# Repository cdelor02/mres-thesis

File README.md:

Thesis for Masters in Research in [Medical Robotics and Image Guided Intervention](https://www.imperial.ac.uk/study/pg/medicine/medical-robotics/) at [Imperial College London](https://www.imperial.ac.uk), 2020-2021.

- Remember to run the setup for EIDORS in MATLAB if it isn't already on the path

Packages and modules used:
- [EIDORS](http://eidors3d.sourceforge.net)
- [gmsh](https://gmsh.info)
- [mesh2matlab](https://github.com/Jimbles/meshio2matlab)
- [OpenCV](https://opencv.org)
- [NumPy](https://numpy.org)
- [Scikit-learn](https://scikit-learn.org/stable/)
- [Tensorflow](https://www.tensorflow.org)
- [Keras](https://keras.io)
- [ffmpeg](https://www.ffmpeg.org)

Resources:
- [Soft robotics toolkit](https://softroboticstoolkit.com/home)

Software used:
- [ParaView](https://www.paraview.org)
- [SolidWorks](https://www.solidworks.com)
- [AutoCAD Inventor (v2021)](https://www.autodesk.co.uk/products/inventor/overview)
- [MATLAB](https://www.mathworks.com/products/matlab.html)
- [LabVIEW](https://www.ni.com/en-gb/shop/labview.html)
- [Arduino](https://www.arduino.cc)

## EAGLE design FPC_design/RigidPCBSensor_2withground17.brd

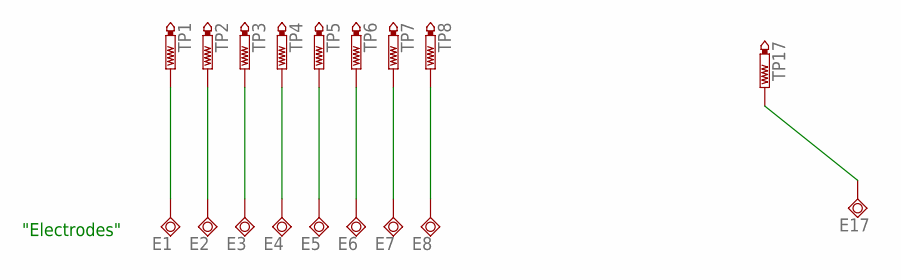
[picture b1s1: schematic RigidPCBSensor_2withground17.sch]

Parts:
E1, E2, E3, E4, E5, E6, E7, E8, E17: TPSQTP15R; TP15R
TP1, TP2, TP3, TP4, TP5, TP6, TP7, TP8, TP17: PTR1; TP10SQLONG

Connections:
unnamed: E1.TP, TP1.TP
unnamed: E2.TP, TP2.TP
unnamed: E3.TP, TP3.TP
unnamed: E4.TP, TP4.TP
unnamed: E5.TP, TP5.TP
unnamed: E6.TP, TP6.TP
unnamed: E7.TP, TP7.TP
unnamed: E8.TP, TP8.TP
unnamed: E17.TP, TP17.TP

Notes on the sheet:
"Electrodes"

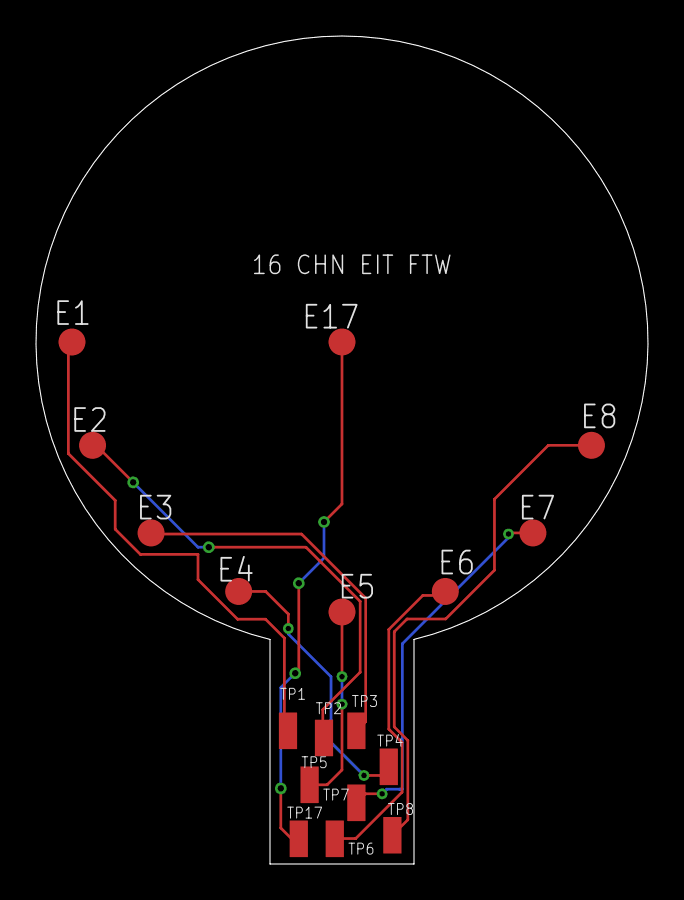
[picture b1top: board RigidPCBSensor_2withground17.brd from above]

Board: 2 copper layers, 34.0 x 46.0 mm, 18 parts (0 on the bottom side), 9 nets.

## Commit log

2021-03-11 start dedicated thesis repo
2021-03-11 simulation work
2021-03-12 sim work
2021-03-16 made hollow version
2021-03-18 work
2021-03-19 Fixed electrode assignment and FWD model check errors in bent finger example
2021-03-20 two bend finger model
2021-03-21 make weekly update presentation
2021-03-23 sim images for slides
2021-03-25 made simple pneunet mesh
2021-03-26 organize and make bent pneunet actuator sim
2021-03-29 second bend pneunet EIDORS model
2021-03-31 weekly meeting
2021-04-06 inflated chambers EIDORS model
2021-04-14 meeting on 14/04/21
2021-04-19 actuator videos
2021-04-21 single chamber EIDORS work
2021-04-22 single chamber stl
2021-04-26 some labview data
2021-04-26 plot labview data
2021-04-27 inflatetest
2021-04-27 labview data
2021-05-05 actuator tube eit data
2021-05-05 general update after weekly meeting
2021-05-10 actuator EIT data
2021-05-17 eit chamber test data
2021-05-25 actuator test eit data
2021-05-28 SDM finger development
2021-06-03 sdm actuator eit test
2021-06-03 fixed sdm actuator eit data
2021-06-03 sdm actuator eit data better
2021-06-07 plots timing test
2021-06-07 parsed/trimmed down actuator data
2021-06-12 poster work
2021-06-23 actuator stepper control
2021-06-29 preliminary full stepper tests
2021-07-01 duetimer test
2021-07-01 more testing
2021-07-06 OpenCV red shape tracking work
2021-07-09 wire impedance measurements with DAQ
2021-07-15 CV progress
2021-07-23 finish cv and neaten up
2021-08-04 create and fill requirements.txt for software
2021-08-04 some eit sync data
2021-08-04 comp vision work
2021-08-06 5 epochs test
2021-08-09 eit data to verify joints
2021-08-09 full test copper_actuator_test_fixed
2021-08-17 500 samples test
2021-08-17 pres updates and actuator progress
2021-08-17 actuator 40Hz eit data
2021-08-18 upload data, fix git access issue
2021-08-18 check git is fine
2021-08-20 camera calib work
2021-08-24 joint-angle measuring w protractor
2021-08-25 aruco work and actuator modeling
2021-08-25 pptx
2021-08-25 angle meas dirs
2021-08-25 indiv angle meas
2021-08-26 redid a0 joint angle acquisition
2021-08-26 actuator iteration experiments
2021-08-27 fixed a0 experiments
2021-09-01 multiple 10iteration experiments for ML
2021-09-02 prelim fixed actuator data
2021-09-02 a2 bend voltages
2021-09-03 bend angle meas in one day
2021-09-05 sunday work w aruco tracking
2021-09-06 vertical actuator experiments
2021-09-06 eit chamber glove experiments
2021-09-07 lookup table and experimentation same day
2021-09-08 35fast chamber lookup tbl and experiments
2021-09-10 experiments (messed up a0)
2021-09-10 fixed a0 actuator experiments
2021-09-10 actuation experiments different step nums
2021-09-10 actuator rand step experiments
2021-09-18 thesis submission update
